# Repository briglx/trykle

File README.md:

# trykle
Water management controler

Create a local `conf.h` based off of `conf-example.h`

# Setup

Install PubSub Client

On arduino ide, goto tools -> Library
Search for pubsub
Installed v2.8

## Configure MQTT Broker

Create a user and ACL for the user

 Type | Pattern | Read Write 
 -----|---------|------------
 Topic  | user - #  | true /true 

## Docker image

```bash
docker build --pull --rm -f "dockerfile" -t trykle:latest "."
docker run -it --rm trykle:latest
#  docker run -it --privileged -v /dev:/dev --rm trykle:latest
#  docker run -it --privileged -v /dev/bus/usb:/dev/bus/usb --rm trykle:latest

docker run -it --privileged --device="class/DCDE6AF9-6610-4285-828F-CAAF78C424CC" --rm trykle:latest
```

## Arduino CLI

```bash
arduino-cli core install esp8266:esp8266
arduino-cli core list
arduino-cli compile --fqbn arduino:esp8266:esp8266 MyFirstSketch
```

# OpenSprinkler Analysis

Main loop code
- do_setup()
    Clear watchdog flag
    os.begin()
    os.optinos_setup()
    pd.init9) prograData init
    Real time clock sync
    Set last startup time
    Start network
    Sync ntp 
    mqtt init
    reset all stations

- do_loop()
    check flow
    Check ethernet packets
    Check State (AP mode or not)
        if inital. Set ap mode. start_server_ap
        if connecting. start_server_client, or timeout
        if connected. wifi_server->handleClient() or reboot, or timeout
    ui_state_machine()
    os.mqtt.loop()
    Check rain delayed
    Check soil sensor
    Check program Switch status (Stop all, manual start)
    Check if need to run a program based on current time
        ensure station has non-zero time and is not disabled
        Enqueue a program if match
    Check time for any running programs to stop them
    os.apply_all_station_bits() Activate / deactivate valves
    Sync time
    check_network
    check_weather

# Real Time Clock

The Real time clock runs on the I2C protocol

The device address is `0x68`

There are 13 registers
- 00h
- ...
- 13h

Real Time Clock Ic^2 signal
- Power 3.3v
- GND
- SDA Data -> GPIO04 -> D2
- SCK Clock -> GPIO14 -> D5

To read, it looks like you have to write the device address and the regsiter address, then read

The data is coded in binary-coded decimal (BCD)

# MCP23008-e/p PDIP/SOIC

- SCL/SCK Pin 1
- SDA/SI Pin 2
- A2/SO (Hardware address pin) Pin 3
- A1 (Hardware address pin) Pin 4
- A0 (Hardware address pin) Pin 5
- (-)Reset Pin 6 (Need to Keep high)
- VSS (Ground) Pin 9
- GP0 Pin 10
- GP1 Pin 11
- GP2 Pin 12
- GP3 Pin 13
- GP4 Pin 14
- GP5 Pin 15
- GP6 Pin 16
- GP7 Pin 17
- VDD (Power) Pin 18

Device Address
Based on teh A0-1 pins

A0 | A1 | A2 | Decimal | Address
--------------------------------
0  |  0 | 0  | 0       | 0x20
0  |  0 | 1  | 1       | 0x21
0  |  1 | 0  | 2       | 0x22
0  |  1 | 1  | 3       | 0x23
1  |  0 | 0  | 4       | 0x24
1  |  0 | 1  | 5       | 0x25
1  |  1 | 0  | 6       | 0x26
1  |  1 | 1  | 7       | 0x27

Register Address

 Address | Access to
---------|---------- 
00h | IODIR
01h | IPOL
02h | GPINTEN
03h | DEFVAL
04h | INTCON
05h | IOCON
06h | GPPU
07h | INTF
08h | INTCAP (Read-only)
09h | GPIO
0Ah | OLA

Opensprinkler code:

# References

- Example pubsub for mqtt on esp2688 https://github.com/knolleary/pubsubclient/blob/master/examples/mqtt_esp8266/mqtt_esp8266.ino
- Arduino CLI https://arduino.github.io/arduino-cli/latest/getting-started/
- OpenSprinkler repos https://github.com/OpenSprinkler
- PCF8523 Real Time Clock (RTC) Data Sheet https://www.nxp.com/docs/en/data-sheet/PCF8523.pdf
- Adafruit-PCF8523 RTC Breakout PCB Eagle https://github.com/adafruit/Adafruit-PCF8523-RTC-Breakout-PCB
- NTP background https://www.circuitbasics.com/using-an-arduino-ethernet-shield-for-timekeeping/
- Arduino Strings https://majenko.co.uk/blog/evils-arduino-strings
- Arduino Time library docs https://github.com/PaulStoffregen/Time
- C++ Style Guide https://google.github.io/styleguide/cppguide.html
- MCP23008-e/p https://4donline.ihs.com/images/VipMasterIC/IC/MCHP/MCHP-S-A0008004111/MCHP-S-A0008004111-1.pdf?hkey=52A5661711E402568146F3353EA87419
- MCP23008 video demo https://www.youtube.com/watch?v=Sos2ghv80wU
- Adafruit MCP230xx library https://github.com/adafruit/Adafruit-MCP23017-Arduino-Library

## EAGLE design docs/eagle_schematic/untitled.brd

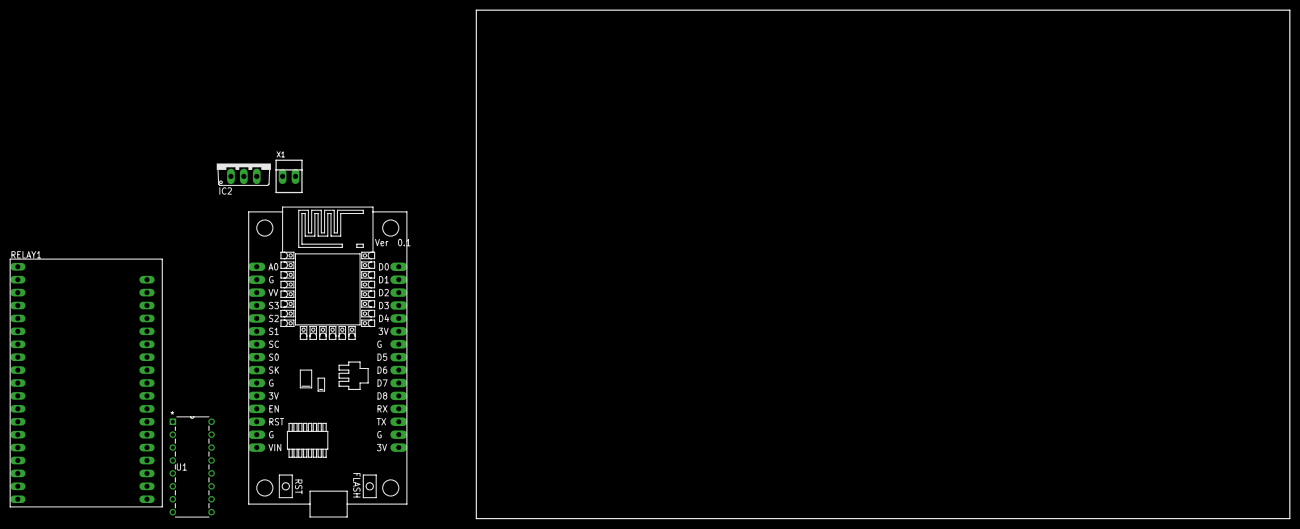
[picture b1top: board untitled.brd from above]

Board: 2 copper layers, 160.0 x 100.0 mm, 5 parts (0 on the bottom side), 2 nets, no tracks yet.

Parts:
IC2: 7805TV; TO220V
RELAY1: RELAY8MODULEDC
U1: SN74HC595N; N16
U$1: NODEMCU
X1: 22-23-2021

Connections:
3V: U$1.11, U$1.16, U$1.25
GND: U1.8, U$1.2, U$1.10, U$1.14, U$1.17, U$1.24

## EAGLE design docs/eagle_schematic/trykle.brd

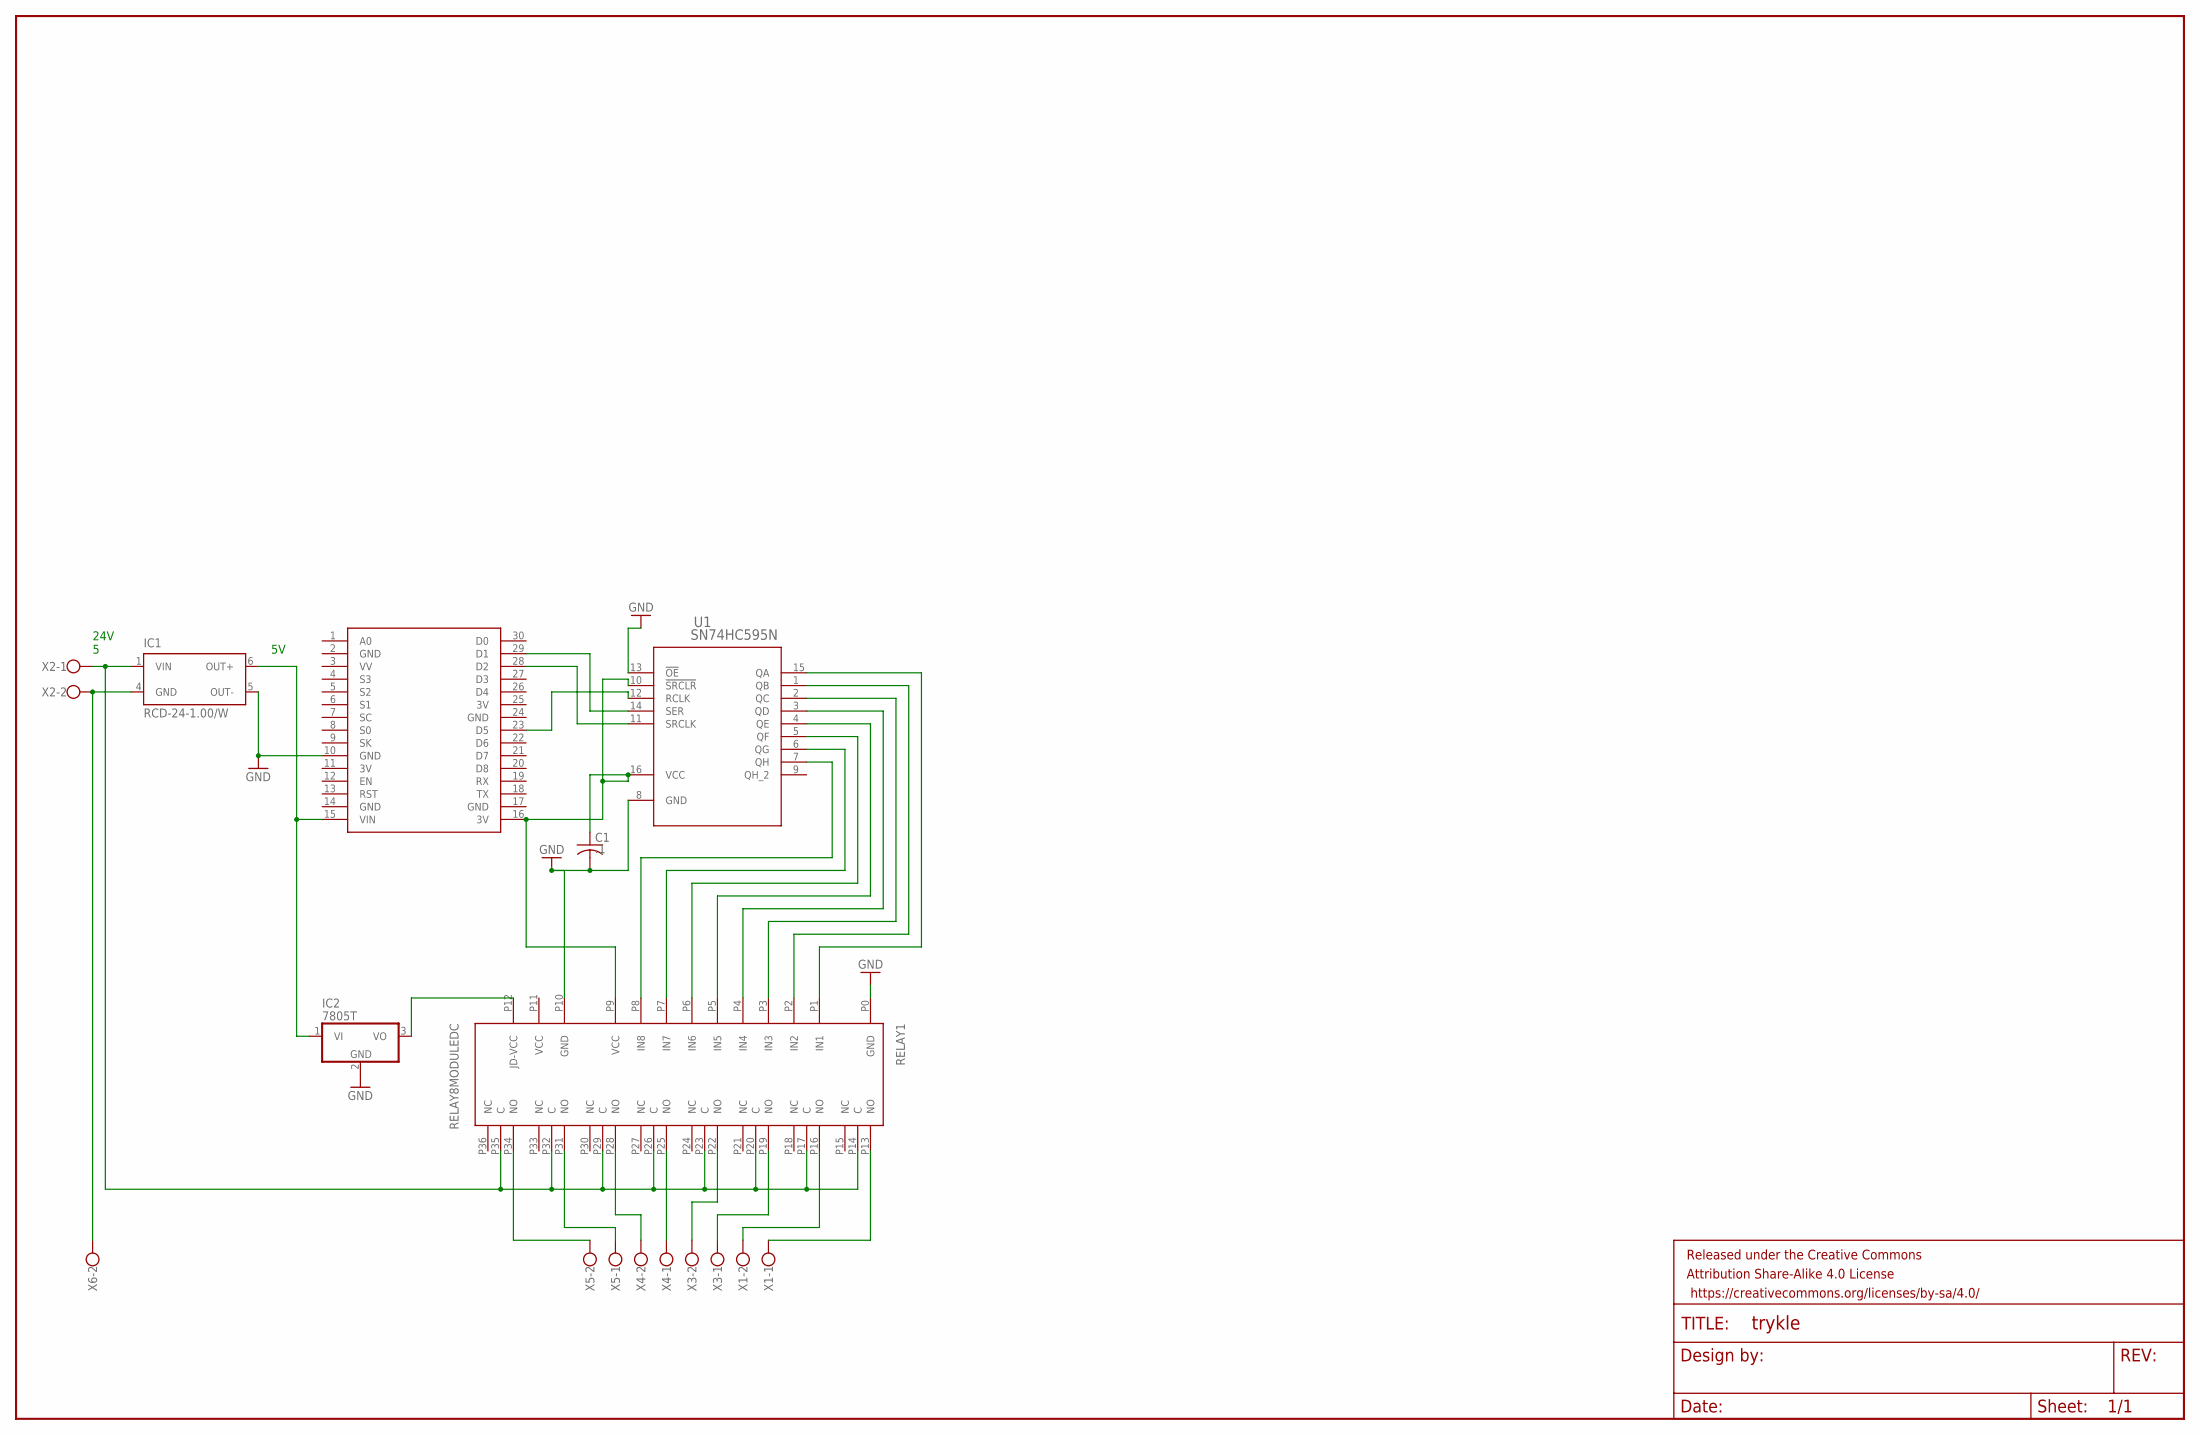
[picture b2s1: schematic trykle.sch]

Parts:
C1: .1; C0805
FRAME1: FRAME-LEDGERNO_FOOTPRINT; DUMMY
IC1: RCD-24-1.00/W; RCD-24/W
IC2: 7805T; TO220H
RELAY1: RELAY8MODULEDC
U1: SN74HC595N; N16
U$2: NODEMCU
X1, X2, X3, X4, X5, X6: W237-102

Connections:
3V: U$2.11 (3V), U$2.25 (3V)
GND: C1.2, IC1.5 (OUT-), IC2.2 (GND), RELAY1.P0 (GND), RELAY1.P10 (GND), U1.8 (GND), U1.13 (!OE), U$2.2 (GND), U$2.10 (GND), U$2.14 (GND), U$2.17 (GND), U$2.24 (GND)
unnamed: IC1.6 (OUT+), IC2.1 (VI), U$2.15 (VIN)
unnamed: RELAY1.P1 (IN1), U1.15 (QA)
unnamed: IC2.3 (VO), RELAY1.P12 (JD-VCC)
unnamed: RELAY1.P2 (IN2), U1.1 (QB)
unnamed: RELAY1.P3 (IN3), U1.2 (QC)
unnamed: RELAY1.P4 (IN4), U1.3 (QD)
unnamed: RELAY1.P5 (IN5), U1.4 (QE)
unnamed: RELAY1.P6 (IN6), U1.5 (QF)
unnamed: RELAY1.P7 (IN7), U1.6 (QG)
unnamed: RELAY1.P8 (IN8), U1.7 (QH)
unnamed: C1.1, RELAY1.P9 (VCC), U1.10 (!SRCLR), U1.16 (VCC), U$2.16 (3V)
unnamed: U1.14 (SER), U$2.29 (D1)
unnamed: U1.11 (SRCLK), U$2.28 (D2)
unnamed: U1.12 (RCLK), U$2.23 (D5)
unnamed: RELAY1.P13 (NO), X1.1
unnamed: RELAY1.P16 (NO), X1.2
unnamed: RELAY1.P19 (NO), X3.1
unnamed: RELAY1.P22 (NO), X3.2
unnamed: RELAY1.P25 (NO), X4.1
unnamed: RELAY1.P28 (NO), X4.2
unnamed: RELAY1.P31 (NO), X5.1
unnamed: RELAY1.P34 (NO), X5.2
unnamed: IC1.4 (GND), X2.2, X6.2
unnamed: IC1.1 (VIN), RELAY1.P14 (C), RELAY1.P17 (C), RELAY1.P20 (C), RELAY1.P23 (C), RELAY1.P26 (C), RELAY1.P29 (C), RELAY1.P32 (C), RELAY1.P35 (C), X2.1

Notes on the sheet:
24V 5

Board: 2 copper layers, 13 parts (1 on the bottom side), 26 nets, no tracks yet.

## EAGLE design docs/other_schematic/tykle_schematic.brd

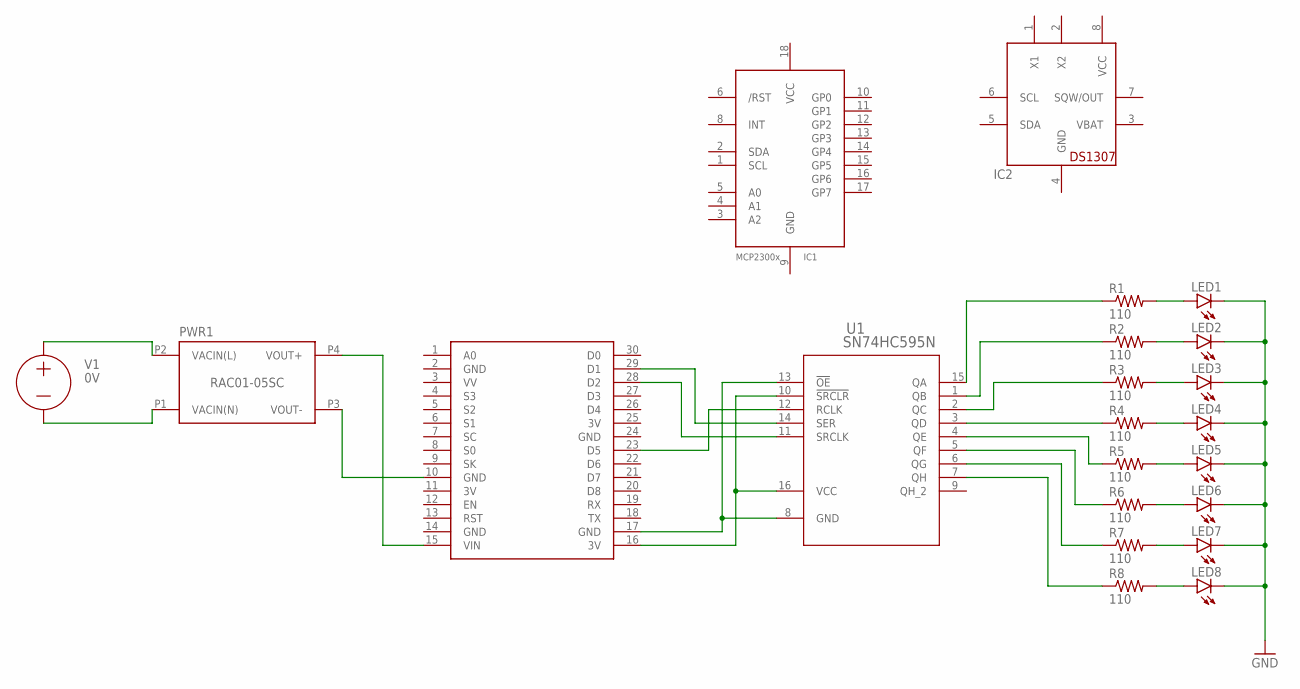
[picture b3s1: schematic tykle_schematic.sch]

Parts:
IC1: MCP23008/P; DIL18
IC2: DS1307; DIL08
LED1, LED2, LED3, LED4, LED5, LED6, LED7, LED8: LED5MM
PWR1: RAC01-05SC; LOW_PROFILE_POWER_MODULE
R1, R2, R3, R4, R5, R6, R7, R8: 110; R0805
U1: SN74HC595N; N16
U$1: NODEMCU

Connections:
3V: U$1.11 (3V), U$1.25 (3V)
GND: IC1.9 (GND), IC2.4 (GND), LED1.K (C), LED2.K (C), LED3.K (C), LED4.K (C), LED5.K (C), LED6.K (C), LED7.K (C), LED8.K (C), U$1.2 (GND), U$1.14 (GND), U$1.24 (GND)
unnamed: PWR1.P4 (VOUT+), U$1.15 (VIN)
unnamed: PWR1.P3 (VOUT-), U$1.10 (GND)
unnamed: U1.8 (GND), U1.13 (!OE), U$1.17 (GND)
unnamed: U1.10 (!SRCLR), U1.16 (VCC), U$1.16 (3V)
unnamed: U1.12 (RCLK), U$1.23 (D5)
unnamed: U1.14 (SER), U$1.29 (D1)
unnamed: U1.11 (SRCLK), U$1.28 (D2)
unnamed: R1.1, U1.15 (QA)
unnamed: R2.1, U1.1 (QB)
unnamed: R3.1, U1.2 (QC)
unnamed: R4.1, U1.3 (QD)
unnamed: R5.1, U1.4 (QE)
unnamed: R6.1, U1.5 (QF)
unnamed: R7.1, U1.6 (QG)
unnamed: R8.1, U1.7 (QH)
unnamed: LED7.A, R7.2
unnamed: LED1.A, R1.2
unnamed: LED2.A, R2.2
unnamed: LED3.A, R3.2
unnamed: LED6.A, R6.2
unnamed: LED5.A, R5.2
unnamed: LED4.A, R4.2
unnamed: LED8.A, R8.2
VBAT: IC2.3 (VBAT)
VCC: IC1.18 (VCC), IC2.8 (VCC)

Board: 2 copper layers, 21 parts (0 on the bottom side), 26 nets, no tracks yet.

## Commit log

2020-09-10 Add main
2020-09-11 Add reference to mqtt on esp2688
2020-09-11 Move secrets out of main
2020-09-11 Move main to subfolder
2020-09-11 Update conf example
2020-09-21 make function
2020-09-21 Add MQTT setup instructions
2020-09-21 Fix markdown table
2020-09-21 Add function and BLINK
2020-09-21 Add additional blinking
2020-09-22 Make event signal
2020-09-23 Add shift demo
2020-09-23 Convert Payload to Int
2020-11-13 Add Webapp
2020-11-13 Move website to own project
2021-07-09 Add real-time clock
2021-07-09 Add ntp sync
2022-11-21 migrate computer

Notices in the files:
parts and their libraries:
SparkFun-Aesthetics: Licensing: Creative Commons ShareAlike 4.0 International - https://creativecommons.org/licenses/by-sa/4.0
SparkFun-Aesthetics: Released under the Creative Commons Attribution Share-Alike 4.0 License
SparkFun-Aesthetics: https://creativecommons.org/licenses/by-sa/4.0
